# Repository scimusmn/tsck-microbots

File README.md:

tsck-microbots
==============

An interactive near-future medical robotics game.

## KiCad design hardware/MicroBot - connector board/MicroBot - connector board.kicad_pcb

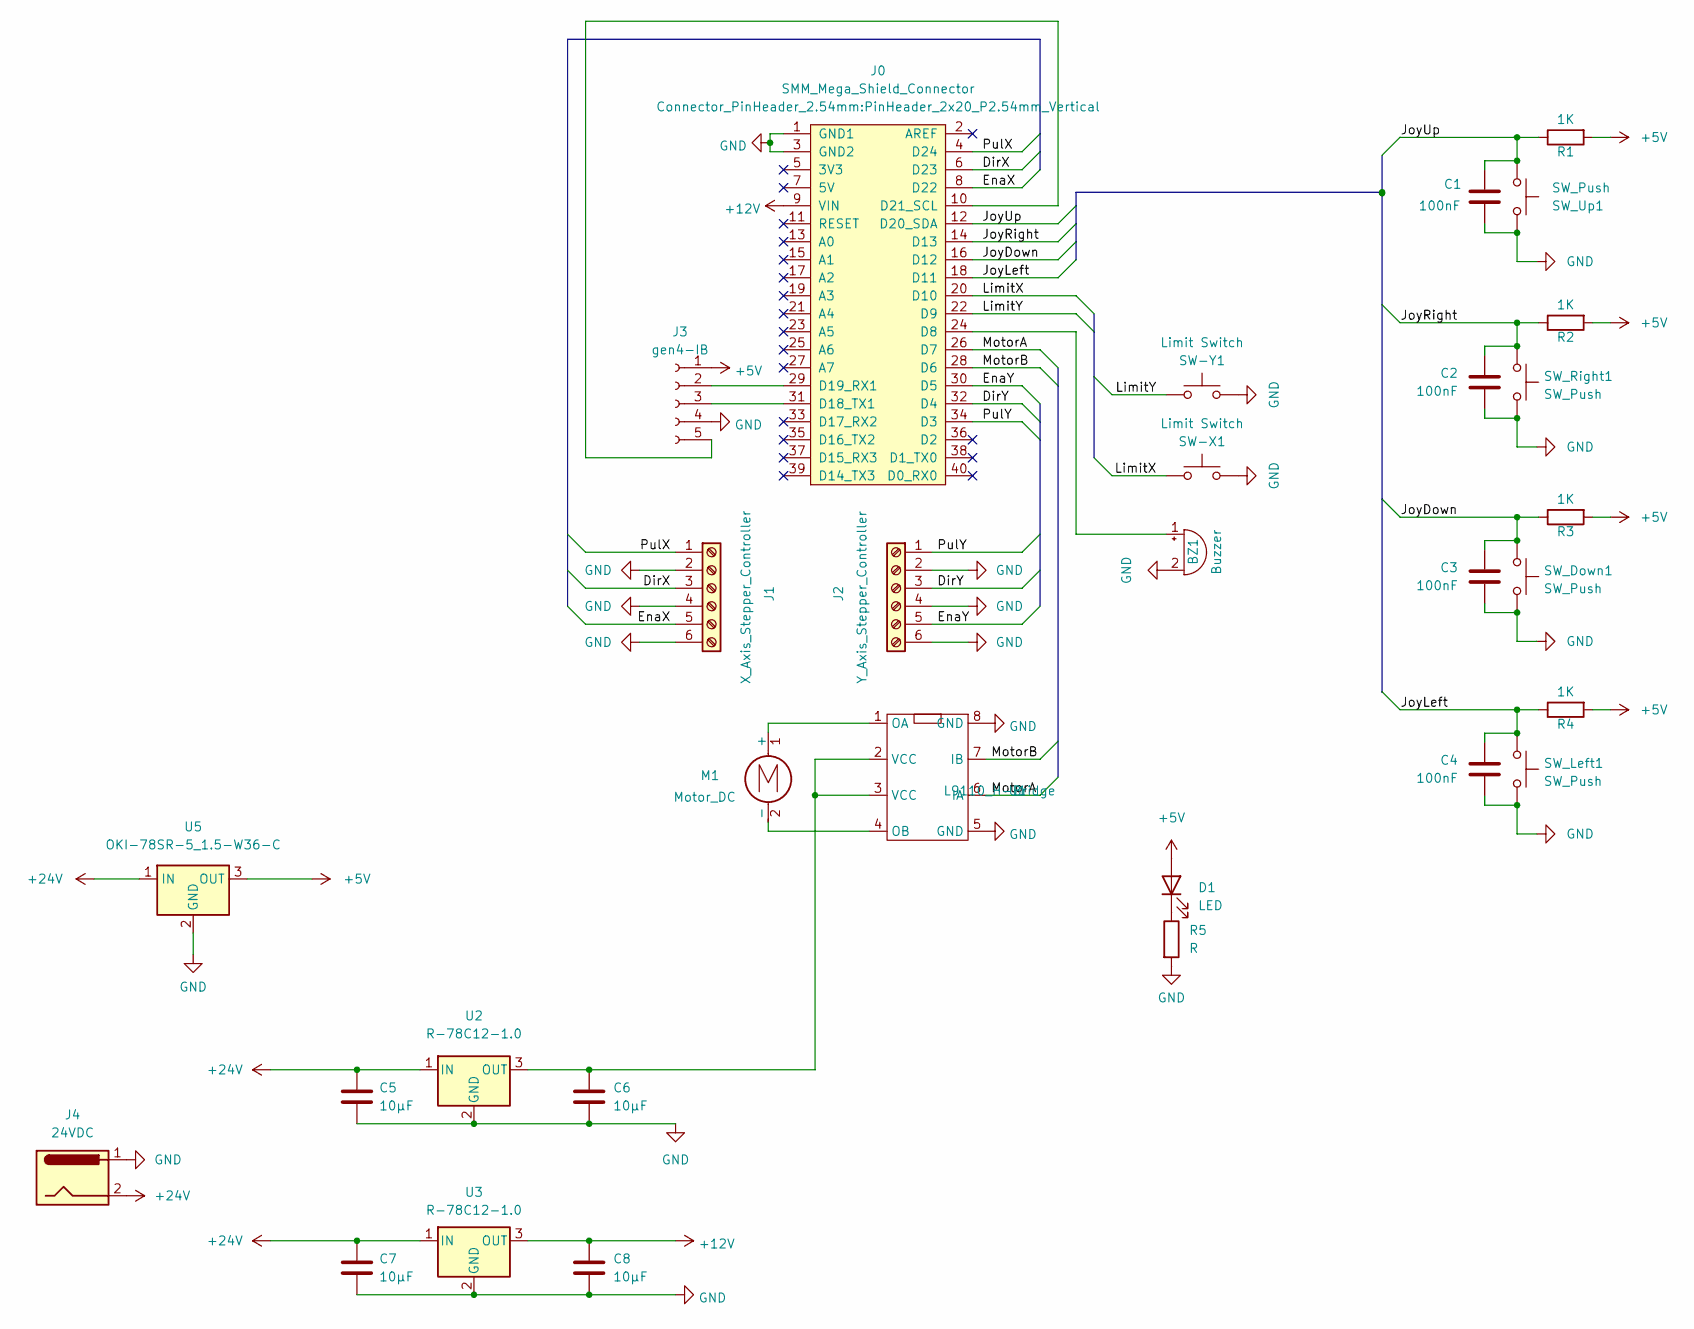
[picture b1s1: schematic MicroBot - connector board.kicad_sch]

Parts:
BZ1: Buzzer; TerminalBlock-2_P5.08mm_small
C1, C2, C3, C4: 100nF; C_Disc_D3.0mm_W2.0mm_P2.50mm
C5, C6, C7, C8: 10µF; CP_Radial_D4.0mm_P1.50mm
D1: LED; LED_D3.0mm
J0: SMM_Mega_Shield_Connector; PinHeader_2x20_P2.54mm_Vertical
J1: X_Axis_Stepper_Controller; TerminalBlock_bornier-6_P5.08mm
J2: Y_Axis_Stepper_Controller; TerminalBlock_bornier-6_P5.08mm
J3: gen4-IB; PinSocket_1x05_P2.54mm_Horizontal
J4: 24VDC; TerminalBlock-2_P5.08mm_large
M1: Motor_DC; TerminalBlock-2_P5.08mm_small
R1, R2, R3, R4: 1K; Resistor_L6.3mm_D2.5mm_P10.16mm_Horizontal
R5: R; Resistor_L6.3mm_D2.5mm_P10.16mm_Horizontal
SW-X1: Limit Switch; TerminalBlock-2_P5.08mm_small
SW-Y1: Limit Switch; TerminalBlock-2_P5.08mm_small
SW_Down1: SW_Push; TerminalBlock-2_P5.08mm_small
SW_Left1: SW_Push; TerminalBlock-2_P5.08mm_small
SW_Right1: SW_Push; TerminalBlock-2_P5.08mm_small
SW_Up1: SW_Push; TerminalBlock-2_P5.08mm_small
U1: L9110_H-Bridge; DIP-8_W7.62mm_Socket
U2, U3: R-78C12-1.0; Converter_DCDC_RECOM_R-78E-0.5_THT
U5: OKI-78SR-5_1.5-W36-C; Converter_DCDC_Murata_OKI-78SR_Vertical

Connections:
+5V: D1.2 (A), J3.1, R1.2, R2.2, R3.2, R4.2, U5.3 (OUT)
+12V: C8.1, J0.9 (VIN), U3.3 (OUT)
+24V: C5.1, C7.1, J4.2, U2.1 (IN), U3.1 (IN), U5.1 (IN)
/DirX: J0.6 (D23), J1.3
/DirY: J0.32 (D4), J2.3
/EnaX: J0.8 (D22), J1.5
/EnaY: J0.30 (D5), J2.5
/JoyDown: C3.2, J0.16 (D12), R3.1, SW_Down1.2
/JoyLeft: C4.2, J0.18 (D11), R4.1, SW_Left1.2
/JoyRight: C2.2, J0.14 (D13), R2.1, SW_Right1.2
/JoyUp: C1.2, J0.12 (D20_SDA), R1.1, SW_Up1.2
/LimitX: J0.20 (D10), SW-X1.1
/LimitY: J0.22 (D9), SW-Y1.1
/MotorA: J0.26 (D7), U1.6 (IA)
/MotorB: J0.28 (D6), U1.7 (IB)
/PulX: J0.4 (D24), J1.1
/PulY: J0.34 (D3), J2.1
GND: BZ1.2 (+), C1.1, C2.1, C3.1, C4.1, C5.2, C6.2, C7.2, C8.2, J0.1 (GND1), J0.3 (GND2), J1.2, J1.4, J1.6, J2.2, J2.4, J2.6, J3.4, J4.1, R5.2, SW-X1.2, SW-Y1.2, SW_Down1.1, SW_Left1.1, SW_Right1.1, SW_Up1.1, U1.5 (GND), U1.8 (GND), U2.2 (GND), U3.2 (GND), U5.2 (GND)
unnamed: BZ1.1 (-), J0.24 (D8)
unnamed: C6.1, U1.2 (VCC), U1.3 (VCC), U2.3 (OUT)
unnamed: D1.1 (K), R5.1
unnamed: J0.10 (D21_SCL), J3.5
unnamed: J0.29 (D19_RX1), J3.2
unnamed: J0.31 (D18_TX1), J3.3
unnamed: M1.1 (+), U1.1 (OA)
unnamed: M1.2 (-), U1.4 (OB)

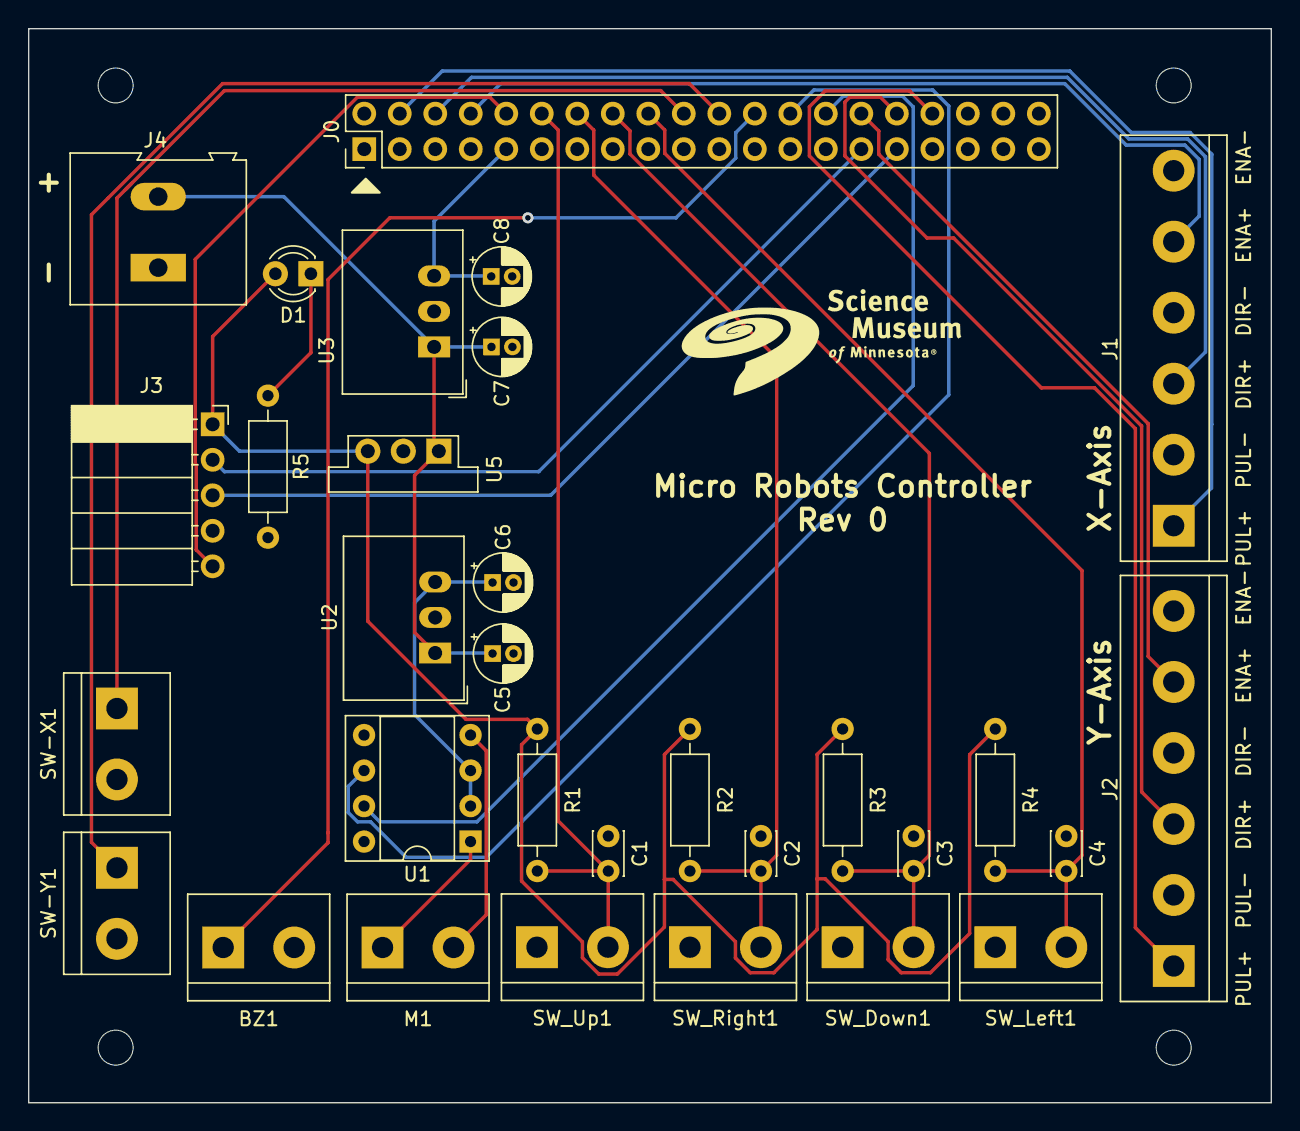
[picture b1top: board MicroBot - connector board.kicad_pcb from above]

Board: 2 copper layers, 88.9 x 76.8 mm, 31 parts (0 on the bottom side), 26 nets.

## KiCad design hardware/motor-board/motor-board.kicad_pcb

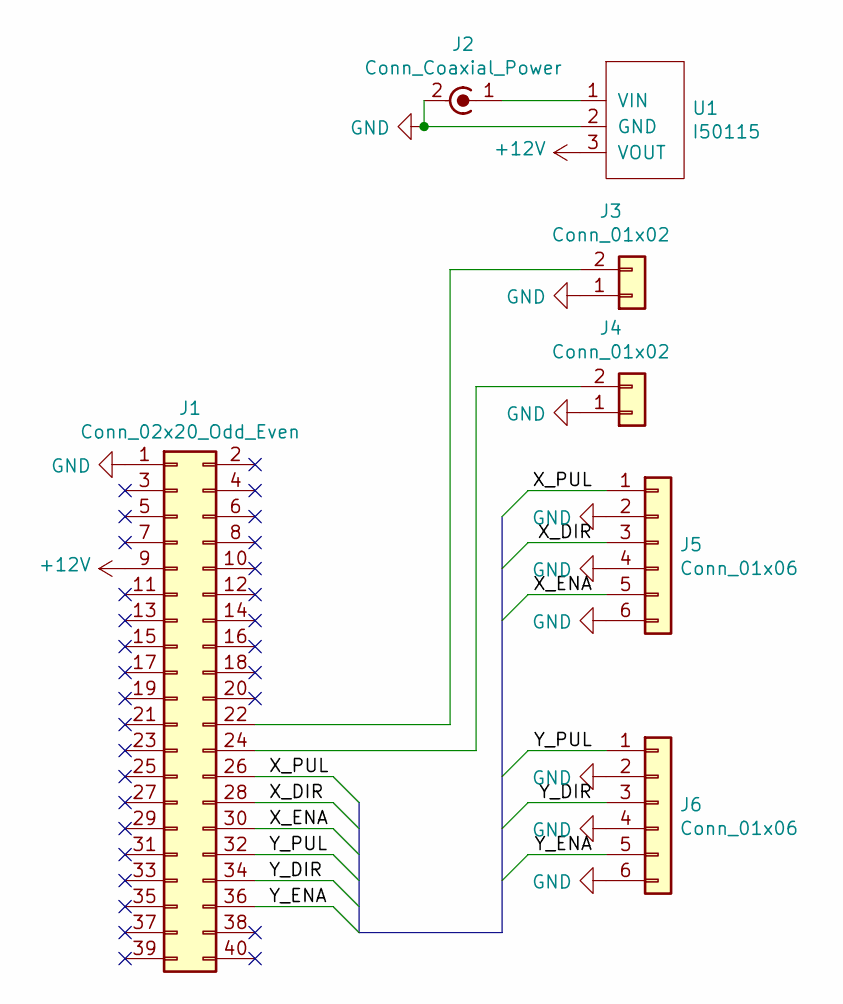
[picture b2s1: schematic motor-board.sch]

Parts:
J1: Conn_02x20_Odd_Even; PinHeader_2x20_P2.54mm_Vertical
J2: Conn_Coaxial_Power; TerminalBlock_bornier-2_P5.08mm
J3, J4: Conn_01x02; TerminalBlock_bornier-2_P5.08mm
J5, J6: Conn_01x06; TerminalBlock_bornier-6_P5.08mm
U1: I50115; PinHeader_1x03_P2.54mm_Vertical

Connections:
+12V: J1.9, U1.3 (VOUT)
/X_DIR: J1.28, J5.3
/X_ENA: J1.30, J5.5
/X_PUL: J1.26, J5.1
/Y_DIR: J1.34, J6.3
/Y_ENA: J1.36, J6.5
/Y_PUL: J1.32, J6.1
GND: J1.1, J2.2 (Ext), J3.1, J4.1, J5.2, J5.4, J5.6, J6.2, J6.4, J6.6, U1.2 (GND)
unnamed: J1.22, J3.2
unnamed: J1.24, J4.2
unnamed: J2.1 (In), U1.1 (VIN)

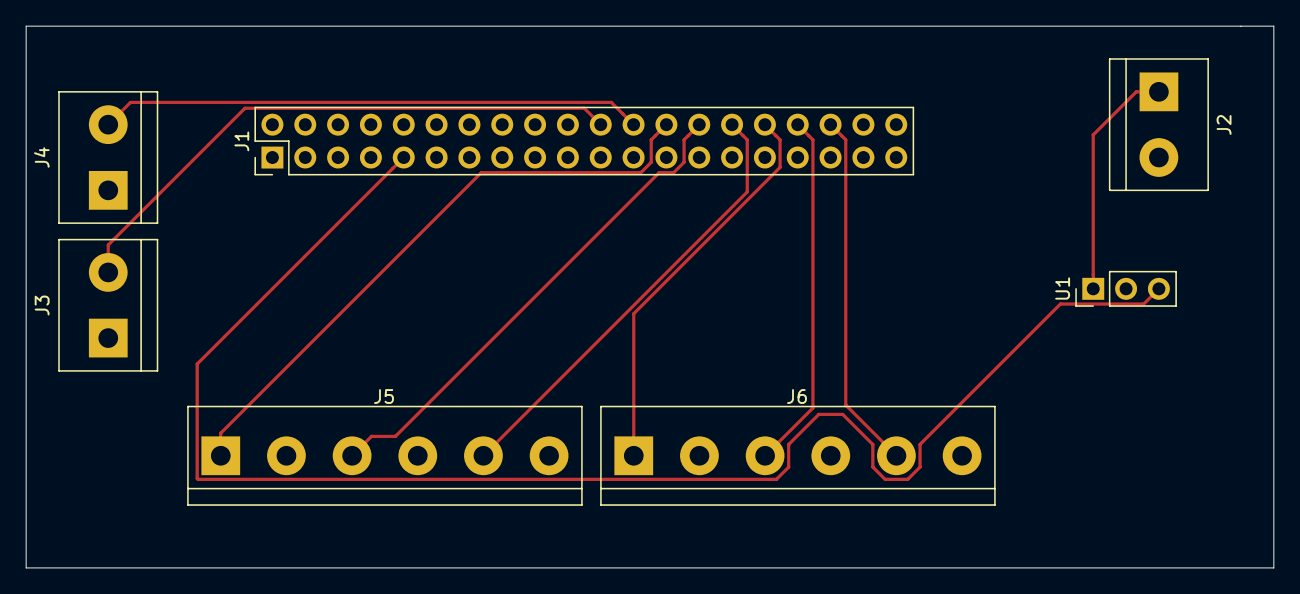
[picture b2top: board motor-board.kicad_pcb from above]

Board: 2 copper layers, 96.5 x 41.9 mm, 7 parts (0 on the bottom side), 11 nets.

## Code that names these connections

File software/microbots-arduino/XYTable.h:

#pragma once

#include <Arduino.h>
#include "Motor.h"
#include "CheckError.h"
#include "Position.h"

#define XY_LOG(msg) LOG("[XYTable] ", msg)

#define Y_PUL 3
#define Y_DIR 4
#define Y_ENA 5
#define Y_LIM 9 

#define X_PUL 24
#define X_DIR 23
#define X_ENA 22
#define X_LIM 10


class XYTable {
	protected:
	Stepper xAxis, yAxis;
	long xMax, yMax;

	int _stepsToPixels(long x, long max) {
		return 127 - ((128*x)/max);
	}

	int _pixelsToSteps(long x, long max) {
		return max - ((max*x)/128);
	}

	public:
	XYTable(long xMax, long yMax)
		: xAxis(X_PUL, X_DIR, X_ENA, X_LIM, xMax
#ifdef MIRROR_TABLE
, true), /* invert x-axis */
#else
),       /* do not invert x-axis */
#endif
		  yAxis(Y_PUL, Y_DIR, Y_ENA, Y_LIM, yMax),
		  xMax(xMax), yMax(yMax)
	{}

	void init() {
		XY_LOG("Homing X...");
		xAxis.home();
		/* move forward, to avoid dragging BBs along the wall */
		xAxis.setSpeed(400);
		while(xAxis.getSteps() < 1000) xAxis.update();
		xAxis.setSpeed(0);
		XY_LOG("Homing Y...");
		yAxis.home();
	}

	Position getPosition() {
		Position pos;
		pos.x = xAxis.getSteps();
		pos.y = yAxis.getSteps();
		return pos;
	}

	Position toPixels(Position stepPos) {
		Position pixelPos;
		pixelPos.x = _stepsToPixels(stepPos.x, xMax);
#ifdef MIRROR_TABLE
		pixelPos.x = 127 - pixelPos.x;
#endif
		pixelPos.y = _stepsToPixels(stepPos.y, yMax);
		return pixelPos;
	}

	Position toSteps(Position pixelPos) {
		Position stepPos;
		stepPos.x = _pixelsToSteps(pixelPos.x, xMax);
#ifdef MIRROR_TABLE
		stepPos.x = xMax - stepPos.x;
#endif
		stepPos.y = _pixelsToSteps(pixelPos.y, yMax);
		return stepPos;
	}

	void setSpeed(int x, int y) {
		xAxis.setSpeed(x);
		yAxis.setSpeed(y);
	}

	void update() {
		xAxis.update();
		yAxis.update();
	}

	void moveTo(long x, long y, int speed) {
		Position current = getPosition();

		int dx = x - current.x;
		int dy = y - current.y;

		/* determine directions */
		int xSpeed = speed;
		int ySpeed = speed;
		if (dx < 0) xSpeed = -speed;
		if (dy < 0) ySpeed = -speed;

		Serial.print("[XYTable] Start position: (");
		Serial.print(current.x); Serial.print(", "); Serial.print(current.y); Serial.println(")");

		Serial.print("[XYTable] Target position: (");
		Serial.print(x); Serial.print(", "); Serial.print(y); Serial.println(")");

		/* step until distances are equal */
		if (abs(dx) > abs(dy)) {
			/* step x first */
			xAxis.setSpeed(xSpeed);
			XY_LOG("Stepping X first");
			while(abs(dx) != abs(dy)) {
				xAxis.update();
				dx = x - xAxis.getSteps();
			}
		}
		else {
			/* step y first */
			yAxis.setSpeed(ySpeed);
			XY_LOG("Stepping Y first");
			while(abs(dx) != abs(dy)) {
				yAxis.update();
				dy = y - yAxis.getSteps();
			}
		}

		xAxis.setSpeed(xSpeed);
		yAxis.setSpeed(ySpeed);
		XY_LOG("Stepping together");
		while (abs(dx) > 2) {
			xAxis.update(); yAxis.update();
			dx = x - xAxis.getSteps();
			dy = y - yAxis.getSteps();
		}

		xAxis.setSpeed(0);
		yAxis.setSpeed(0);
	}
};

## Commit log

2020-08-25 Add buttons, steppers & stage
2020-08-25 add acceleration to Stage
2020-08-25 fix sign error in Stepper.cpp
2020-08-25 add path checking
2020-08-25 add path
2020-09-03 add start and end positions
2020-09-03 fix bug in findPosition function
2022-04-26 mount filesystem
2022-04-28 begin custom serial library
2022-04-29 add cargs and stb_image for image-encoder
2022-04-29 add cmake build
2022-04-29 implement basic GCI conversion
2022-04-30 fix endianness
2022-05-02 add image.*
2022-05-11 setup unit tests and add extract_image test
2022-05-11 change test executable name
2022-05-16 add alpha channel to images
2022-05-16 use struct point_t instead of individual numbers in extract_subimage
2022-05-16 add combine_images()
2022-05-16 add convert_gci
2022-05-16 fix free -> free_gci
2022-05-16 refactor: move files into subdirectories
2022-05-16 implement working image encoder
2022-05-16 add explicit labels and omit label array for single images
2022-05-16 improve comments for image-encoder
2022-05-18 add allocate_image() and gci_to_image()
2022-05-18 add alpha_blend() and add_background()
2022-05-23 compile proc.c
2022-05-23 begin cleanup of Screen.h
2022-05-23 reorganize folders
2022-05-23 fix bug in combine_images()
2022-05-23 add generate.sh and make digits.png transparent
2022-05-23 add DiabloSerial.h
2022-05-23 add colon
2022-05-23 remove spurious files and center digits
2022-05-23 add display_time()
2022-05-24 add fs_read_file() and modify for Mega
2022-05-31 path-encoder
2022-05-31 add binary output
2022-05-31 add path loading
2022-05-31 add basic MVC Game.h
2022-05-31 add health readout and heart image
2022-06-06 add game over
2022-06-07 implement full microbots game
2022-06-13 add sounds
2022-06-14 fix path alignment
2022-06-14 add first-pass PCB layout
2022-06-17 update heart path and add continuous buzzing
2022-06-17 finalize board layout
2022-07-12 update ScreenView with new graphics
2022-07-12 update Game.h to reflect changes to ScreenView
2022-07-12 add final graphics images
2022-07-12 fix error in PCB layout
2022-07-12 fix bug in path-encoder
2022-07-12 fix some type-safety warnings
2022-07-12 add Position type and return on serial error
2022-07-12 add compile/upload scripts
2022-08-03 add updated assets
2022-08-03 fix OOB bug
2022-08-03 fix motor sticking bug
2022-08-03 remove MIRROR_TABLE macro definition
2022-10-12 add README.md
2022-10-12 add software/README.md
2022-10-12 add gci-encoder README.md
2022-10-12 add path-encoder README.md
2022-10-12 add game timeout
2022-10-12 update images
2022-10-12 add arduino README.md
